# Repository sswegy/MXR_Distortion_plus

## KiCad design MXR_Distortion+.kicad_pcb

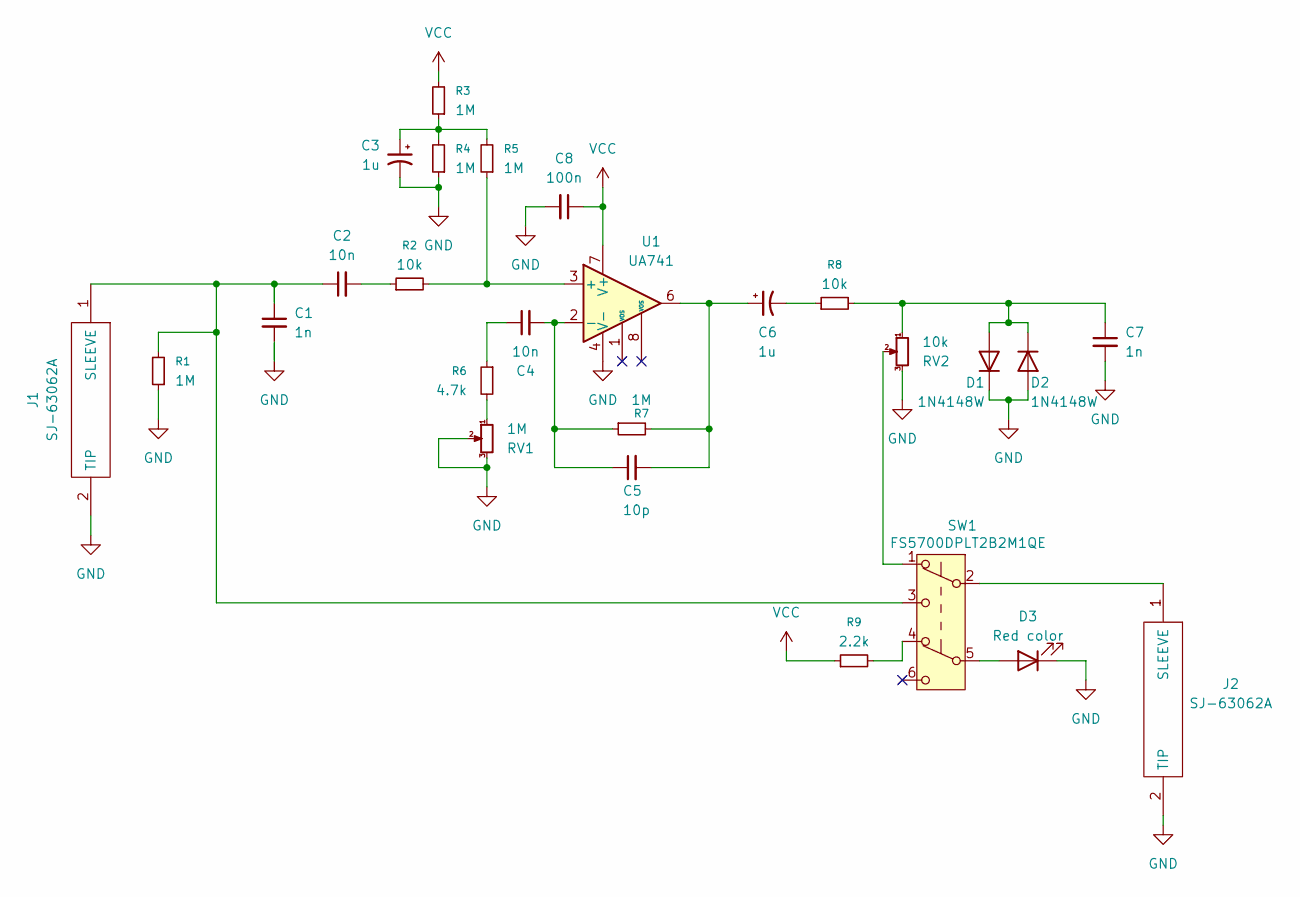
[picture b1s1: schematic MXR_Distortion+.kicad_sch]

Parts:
C1, C7: 1n; C_0805_2012Metric_Pad1.18x1.45mm_HandSolder; Manufacturer_Part_Number C0805X102F5GECTU
C2, C4: 10n; C_0805_2012Metric_Pad1.18x1.45mm_HandSolder; Manufacturer_Part_Number C0805X103F5GACTU
C3, C6: 1u; C_0805_2012Metric_Pad1.18x1.45mm_HandSolder; Manufacturer_Part_Number C0805X105J5RACAUTO
C5: 10p; C_0805_2012Metric_Pad1.18x1.45mm_HandSolder; Manufacturer_Part_Number C0805C100C2GACTU
C8: 100n; C_0805_2012Metric_Pad1.18x1.45mm_HandSolder; Manufacturer_Part_Number C0805C104J5RAC3123
D1, D2: 1N4148W; D_SOD-123; Manufacturer_Part_Number 1N4148W
D3: Red color; LED_D3.0mm_Clear
J1, J2: SJ-63062A; SJ63062A; Manufacturer_Part_Number SJ-63062A; Mouser Part Number 490-SJ-63062A
R1, R3, R4, R5, R7: 1M; R_0805_2012Metric_Pad1.20x1.40mm_HandSolder; Manufacturer_Part_Number RT0805FRE131ML
R2, R8: 10k; R_0805_2012Metric_Pad1.20x1.40mm_HandSolder; Manufacturer_Part_Number RT0805FRE1010KL
R6: 4.7k; R_0805_2012Metric_Pad1.20x1.40mm_HandSolder; Manufacturer_Part_Number RT0805FRE134K7L
R9: 2.2k; R_0805_2012Metric_Pad1.20x1.40mm_HandSolder; Manufacturer_Part_Number RT0805FRE132K2L
RV1: 1M; PDB12H4301105BF; Manufacturer_Part_Number PDB12H4301105BF
RV2: 10k; PDB12H4301103BF; Manufacturer_Part_Number PDB12H4301103BF
SW1: FS5700DPLT2B2M1QE; Manufacturer_Part_Number FS5700DPLT2B2M1QE
U1: UA741; SOIC127P600X175-8N; Manufacturer_Part_Number UA741CD

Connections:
GND: C1.2, C3.2, C7.2, C8.2, D1.1 (K), D2.2 (A), D3.1 (K), J1.2 (TIP), J2.2 (TIP), R1.1, R4.1, RV1.2, RV1.3, RV1.MH1, RV1.MH2, RV2.3, RV2.MH1, RV2.MH2, U1.4 (V-); also elsewhere on the board
unnamed: C2.2, R2.1
unnamed: C3.1, R3.1, R4.2, R5.2
unnamed: C4.1, R6.1
unnamed: C5.2, C6.1, R7.2, U1.6
unnamed: C6.2, R8.1
unnamed: C7.1, D1.2 (A), D2.1 (K), R8.2, RV2.1
unnamed: D3.2 (A), SW1.5 (B)
unnamed: C1.1, C2.1, J1.1 (SLEEVE), R1.2, SW1.3 (C)
unnamed: J2.1 (SLEEVE), SW1.2 (B)
unnamed: R6.2, RV1.1
unnamed: R9.2, SW1.4 (A)
unnamed: RV2.2, SW1.1 (A)
unnamed: R2.2, R5.1, U1.3 (+)
unnamed: C4.2, C5.1, R7.1, U1.2 (-)
VCC: C8.1, R3.2, R9.1, U1.7 (V+); also elsewhere on the board

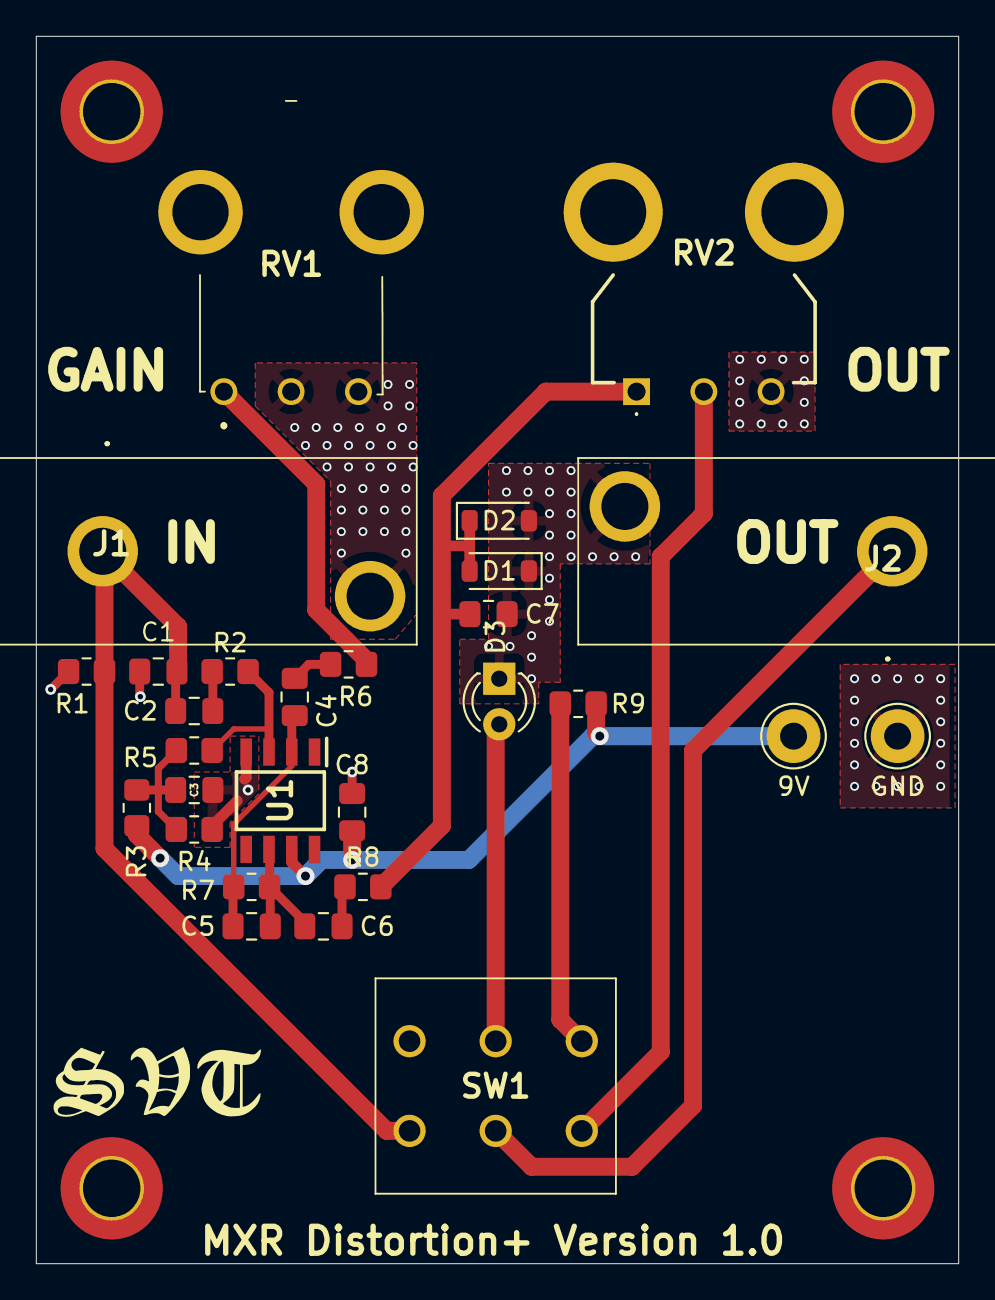
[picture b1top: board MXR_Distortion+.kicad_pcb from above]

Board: 2 copper layers, 51.4 x 68.4 mm, 28 parts (0 on the bottom side), 16 nets.

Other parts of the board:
9V: Pin_D1.3mm_L11.0mm_LooseFit
GND: Pin_D1.3mm_L11.0mm_LooseFit

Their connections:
GND: GND.1; also elsewhere on the board
VCC: 9V.1; also elsewhere on the board

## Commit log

2026-01-22 Add project version 1.0 files
2026-01-22 remove gitignore files
